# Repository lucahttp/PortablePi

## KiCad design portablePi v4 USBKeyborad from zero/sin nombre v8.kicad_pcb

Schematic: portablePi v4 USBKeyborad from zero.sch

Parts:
DS1: 3.5_Inch_RPI; 3.5 inch RPi LCD
IC1: Raspberry_Pi_Zero_W_(v1.3); RASPBERRY_PI_ZERO_W; Manufacturer_Part_Number Raspberry Pi Zero W (v1.3)
J1: AudioJack3; Jack_3.5mm_Ledino_KB3SPRS_Horizontal
SW0, SW1, SW2, SW3, SW4, SW5, SW6, SW7, SW8, SW9, SW10, SW11, SW12, SW13, SW14, SW15, SW16, SW17, SW18, SW19, SW20, SW21, SW22, SW23, SW24, SW25, SW26, SW27, SW28, SW29, SW30, SW31, SW32, SW33, SW34, SW35, SW36, SW37, SW38, SW39, SW40, SW41, SW42, SW43, SW44, SW45, SW46, SW47, SW48, SW49, SW50, SW51, SW52, SW53, SW54, SW55, SW56: SW_Push; SW_PUSH_6mm
U1: ATmega328P-PU; DIP-28_W7.62mm

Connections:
+3V3: DS1.1, DS1.17, IC1.1 (+3.3V_1), IC1.17 (+3.3V_2)
+5V: DS1.2, DS1.4, IC1.2 (+5V_1), IC1.4 (+5V_2)
Col0: SW40.1, SW41.1, SW42.1, SW43.1, SW44.1, SW45.1, SW46.1, SW47.1, SW48.1, SW49.1
Col1: SW50.1, SW51.1, SW52.1, SW53.1, SW54.1, SW55.1, SW56.1
Col2: SW0.1, SW1.1, SW2.1, SW3.1, SW4.1, SW5.1, SW6.1, SW7.1, SW8.1, SW9.1
Col3: SW10.1, SW11.1, SW12.1, SW13.1, SW14.1, SW15.1, SW16.1, SW17.1, SW18.1, SW19.1
Col4: SW20.1, SW21.1, SW22.1, SW23.1, SW24.1, SW25.1, SW26.1, SW27.1, SW28.1, SW29.1
Col5: SW30.1, SW31.1, SW32.1, SW33.1, SW34.1, SW35.1, SW36.1, SW37.1, SW38.1, SW39.1
GND: DS1.6, DS1.9, DS1.14, DS1.20, DS1.25, IC1.6 (GND_1), IC1.9 (GND_2), IC1.14 (GND_3), IC1.20 (GND_4), IC1.25 (GND_5)
LCD_CS: DS1.24, IC1.24 (GPIO_8/SPI0_CE1_N)
LCD_RS: DS1.18, IC1.18 (GPIO_24)
LCD_SCK: DS1.23, IC1.23 (GPIO_11/SPI0_SCLK)
unnamed: U1.8 (GND), U1.22 (GND)
Osc1: U1.9 (XTAL1/PB6)
Osc2: U1.10 (XTAL2/PB7)
RST: DS1.22, IC1.22 (GPIO_25)
Reset: U1.1 (~RESET~/PC6)
Serial_RX: U1.2 (PD0)
Serial_TX: U1.3 (PD1)
TP_CS: DS1.26, IC1.26 (GPIO_7/SPI0_CE2_N)
TP_IRQ: DS1.11, IC1.11 (GPIO_17/SPI1_CS1)
TP_SO: DS1.21, IC1.21 (GPIO_9/SPI0_MISO)
USB_D+: U1.4 (PD2)
USB_D-: U1.5 (PD3)

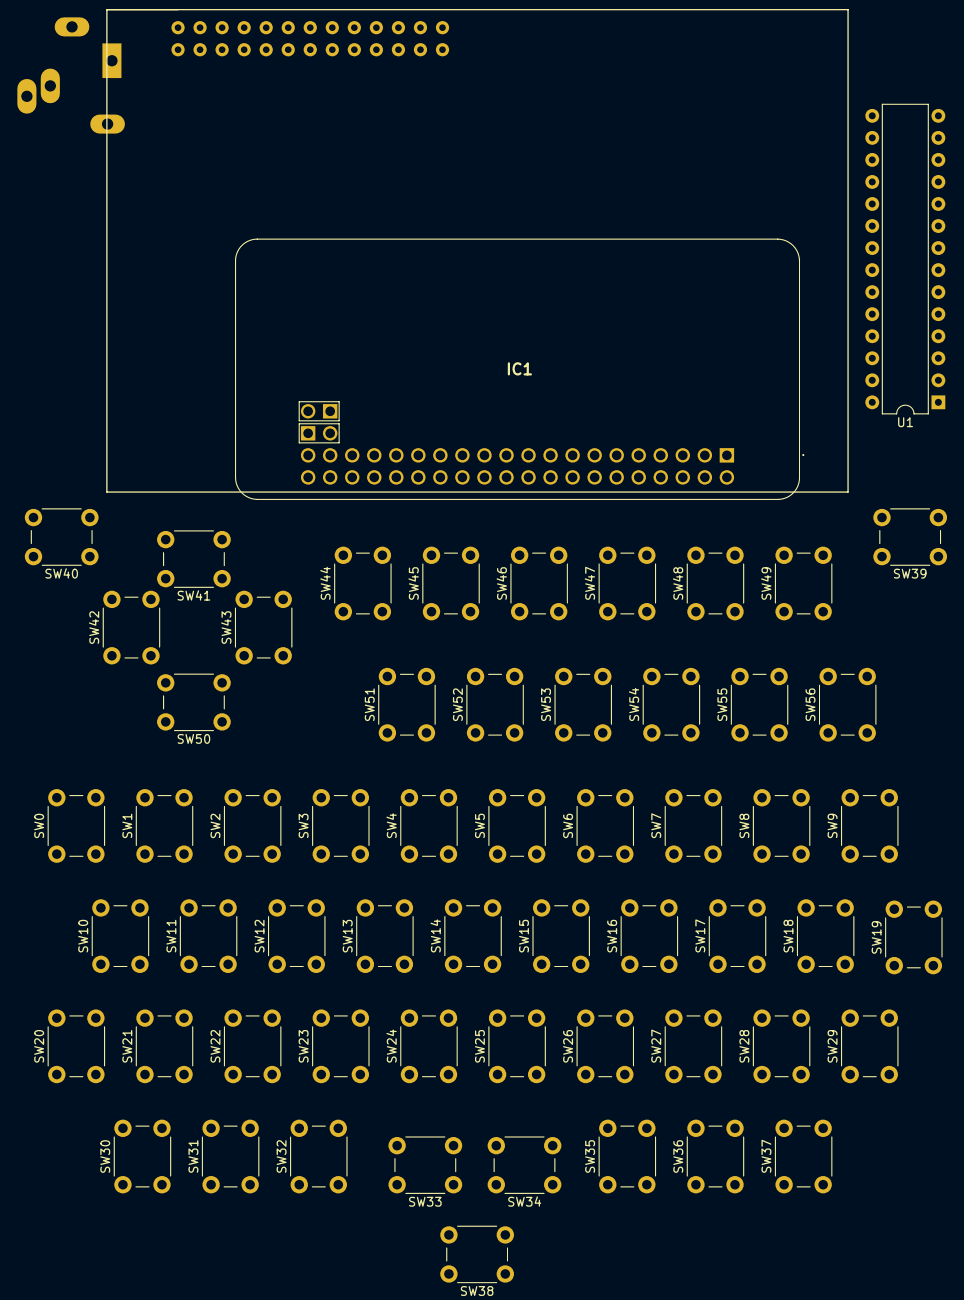
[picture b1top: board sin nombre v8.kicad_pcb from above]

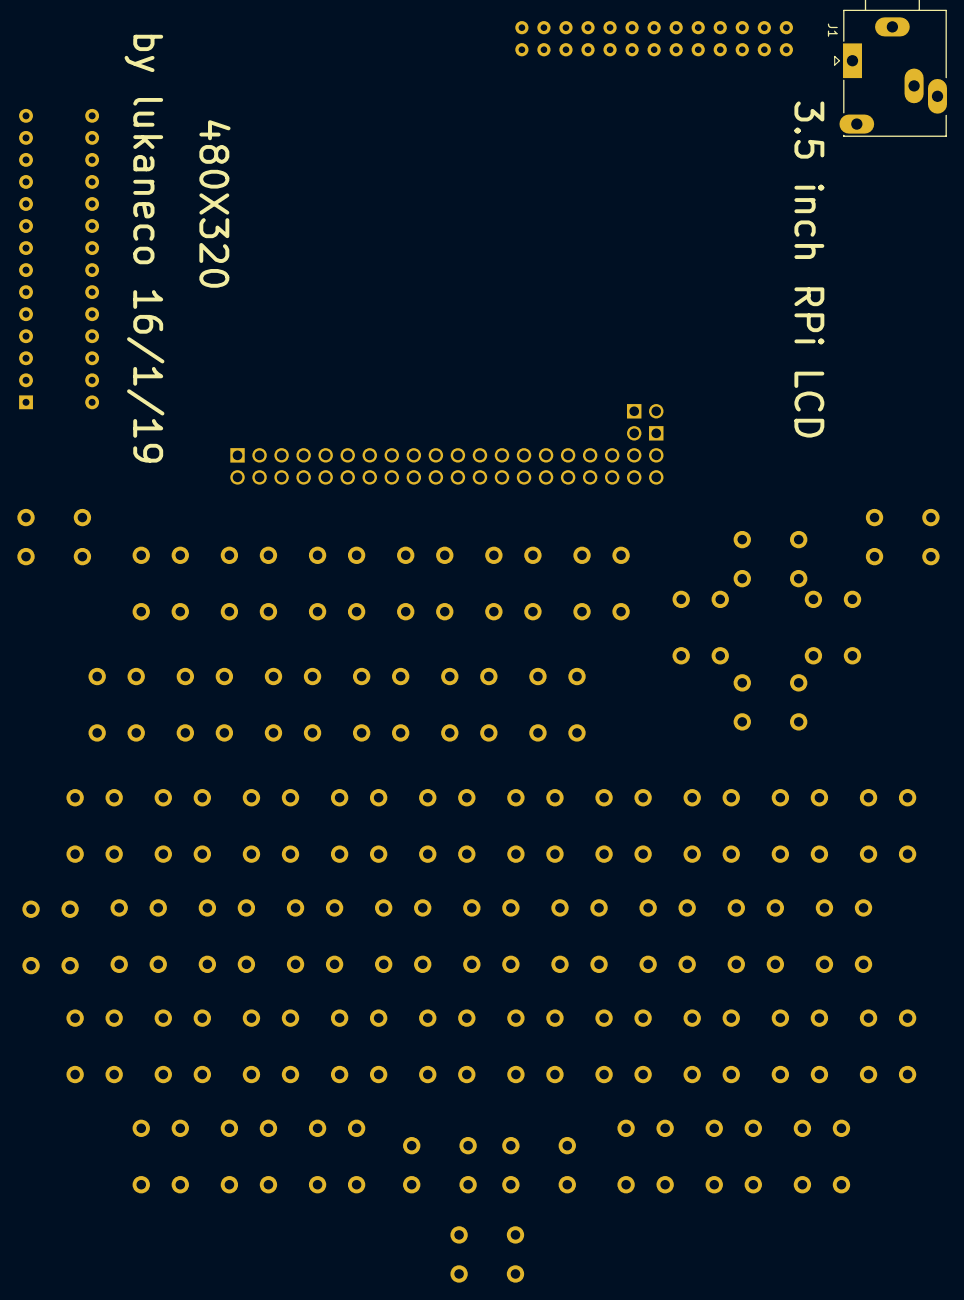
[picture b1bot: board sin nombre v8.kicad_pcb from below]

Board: 2 copper layers, 61 parts (2 on the bottom side), 17 nets, no tracks yet.

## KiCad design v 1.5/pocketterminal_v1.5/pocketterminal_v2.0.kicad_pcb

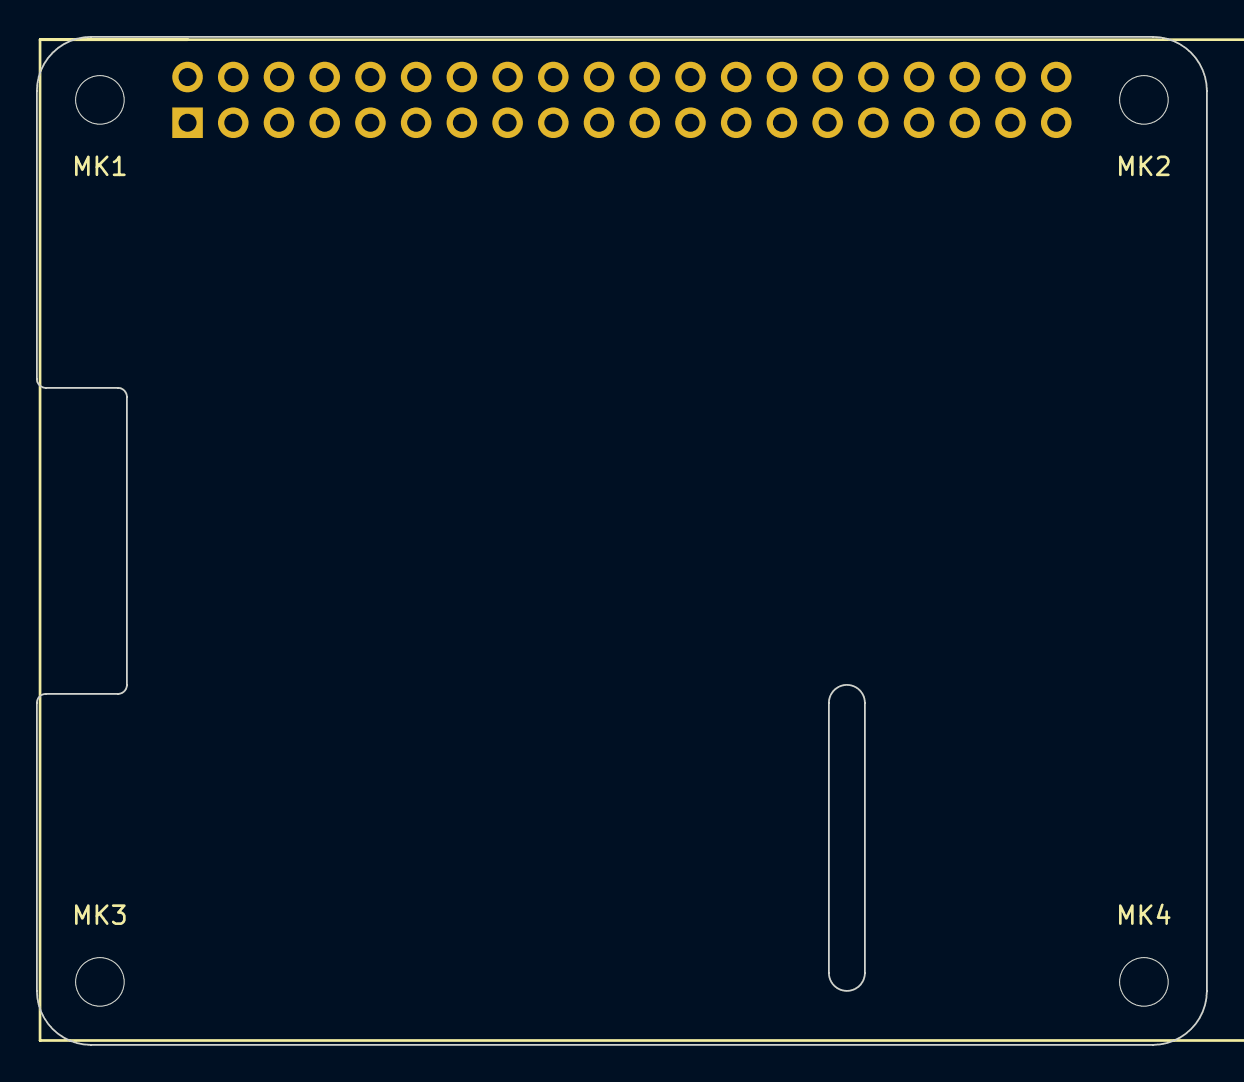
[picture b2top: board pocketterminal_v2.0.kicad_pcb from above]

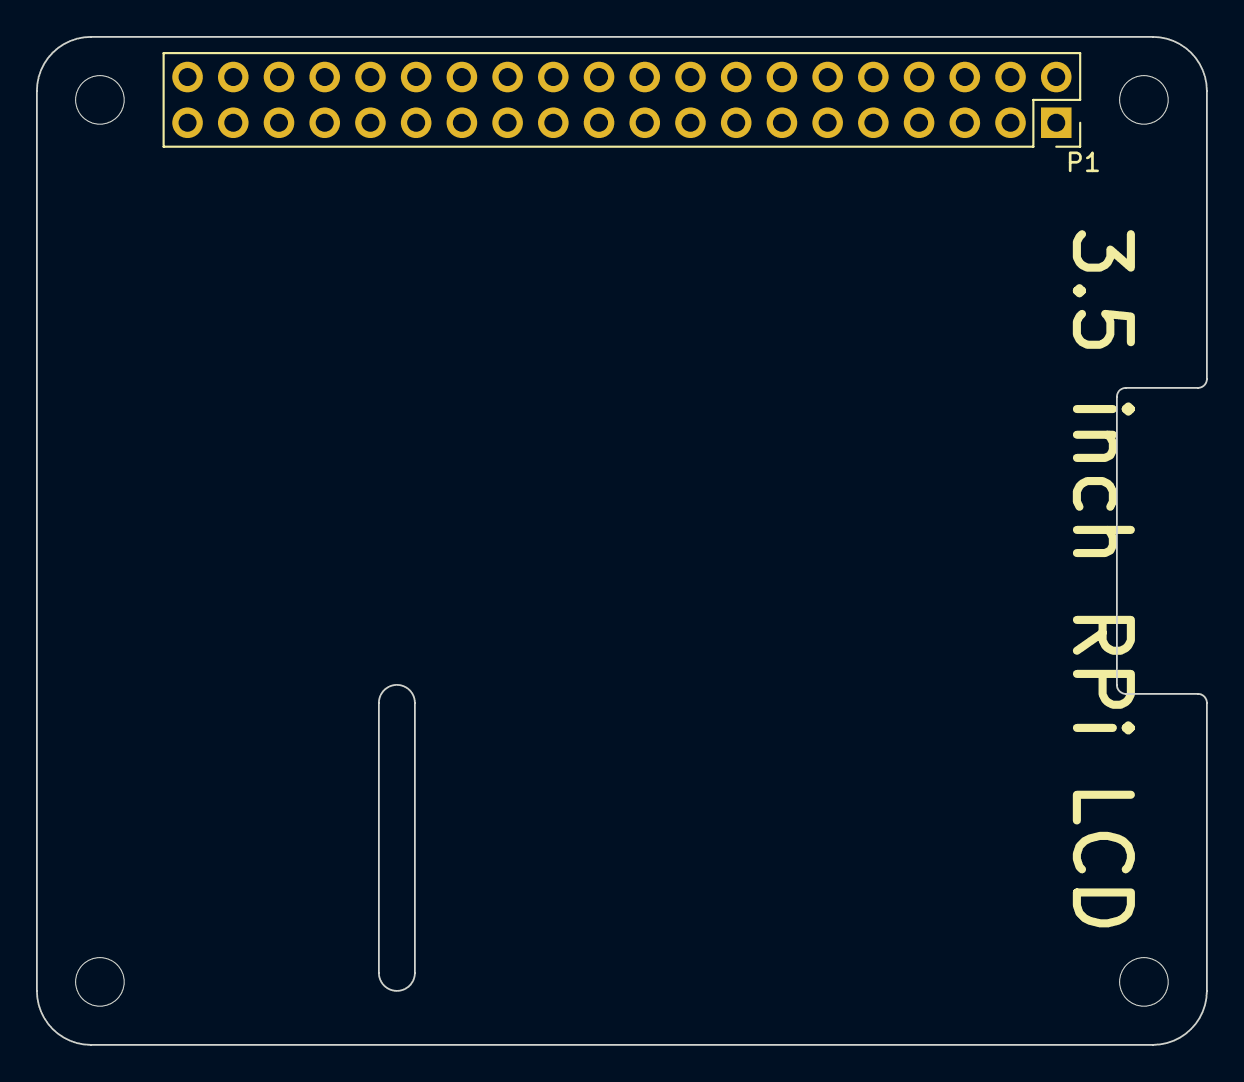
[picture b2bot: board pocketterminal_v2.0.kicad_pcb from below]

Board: 2 copper layers, 65.0 x 56.0 mm, 6 parts (2 on the bottom side), 10 nets, no tracks yet.

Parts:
DS1: 3.5_Inch_RPI; 3.5 inch RPi LCD
MK1, MK2, MK3, MK4: M2.5; MountingHole_2.7mm_M2.5
P1: Conn_02x20_Odd_Even; PinSocket_2x20_P2.54mm_Vertical

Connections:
+3V3: DS1.1, DS1.17, P1.1, P1.17
+5V: DS1.2, DS1.4, P1.2, P1.4
/GPIO7(SPI1_CE_N): DS1.26, P1.26
/GPIO8(SPI0_CE_N): DS1.24, P1.24
/GPIO9(SPI0_MISO): DS1.21, P1.21
/GPIO11(SPI0_SCK): DS1.23, P1.23
/GPIO17(GEN0): DS1.11, P1.11
/GPIO24(GEN5): DS1.18, P1.18
/GPIO25(GEN6): DS1.22, P1.22
GND: DS1.6, DS1.9, DS1.14, DS1.20, DS1.25, P1.6, P1.9, P1.14, P1.20, P1.25, P1.30, P1.34, P1.39
